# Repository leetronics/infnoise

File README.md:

### Infinite Noise TRNG (True Random Number Generator)

For instructions for compiling the and using Infinite Noise TRNG driver, go to the software
sub-directory, and read the [README](software/README.md) file there.  Both Linux and Windows
are supported.

The Infinite Noise TRNG is a USB key hardware true random number generator.  It uses what
I call a "Modular Entropy Multiplier" architecture (previously Infinite Noise Multiplier or
FireBug).  Besides being simple, low-cost, and fast, it is much easier to get right than
other TRNGs.  It naturally defends against influence from outside signals, such as radio
interference and power supply noise, making it simple to build securely, without requiring
an expert in analog design.  Modular entropy multipliers produce a provable and easily
measured level of entropy based on thermal noise, approximately equal to log2(K) per
output bit, where K is a gain between 1 and 2 set by two resistors around an op-amp.  A
"health monitor" can track this and verify that the output entropy is within the expected
range, which for the Infinite Noise TRNG described below is within 2% of log2(1.82).

Modular entropy multipliers are suitable for both board level implementation and ASIC
implementation.  Speed is limited by the speed of a gain stage and a comparator, and can
run in excess of 100 Mbit/second per second with high performance components.  Cheap
solutions with CMOS quad op-amps can run at 8Mbit/second.

Adjacent bits from a modular entropy multiplier are correlated, so whitening is required
before use in cryptography.  This should be done by continually reseeding a
cryptographically secure hash function such as SHA-512, Blake2b, Keccak-1600 (SHA3), or a
stream cipher such as ChaCha.  This implementation uses Keccak-1600 with cryptographically
secure reseeding of more than 400 bits of entropy at a time, overcoming a trickle in/out
problem present in the GNU/Linux /dev/random system.  Users who need many megabytes per second
of data for use in cryptography can set the outputMultiplier as high as they like, which
causes Keccak to generate outputMultiplier\*256 bits per reseeding by the Infinite Noise
TRNG.

The modular entropy multiplier architecture was invented by Peter Allan in 1999, which he
called [Firebug](http://apa.hopto.org/firebug).  I reinvented it in 2013.  As usual, most
of my good ideas are rediscoveries of existing ideas :-)  Peter has his own
version called [the Redoubler](https://github.com/alwynallan/redoubler), which
is awesome.  It really is the _right_ way to generate random bits, whether on a
board with standard parts, or on an custom chip.

### Crowd Supply campaign

With the aid of crowdfunding, the Infinite Noise will soon be produced (again)! The campaign is driven by Manuel Domke, founder of a fresh electronics manufacturing company called 13-37.org electronics. 

[Check the Crowd Supply project page for latest updates](https://www.crowdsupply.com/13-37/infinite-noise-trng)

### The Eagle open-source boards work!

Here is the first completed Infinite Noise USB key.  I offered this model on
Tindie to help get the modular entropy multiplier concept out there initially.

Here are the first three boards from OSH Park.  They work _exactly_ as predicted.  They all
generate 300,000 bits per second, resulting in a measured 259,000 bits of entropy per second, which is within 0.5% of the predicted value of log2(1.82).

All three boards should produce log2(1.82) = 0.864 bits of entropy per bit by design.  The first one is estimated
to produce 0.867, while the second one produces 0.868, and the third is 0.867.

Here is the latest schematic:

![Schematic of Infinite Noise Multiplier](images/infnoise.png?raw=true "Infinite
Noise Multiplier")

Here is the latest board layout (thanks, EagleWorks!):

![Board layout of Infinite Noise Multiplier](images/infnoise_brd.png?raw=true "Infinite
Noise Multiplier")

The breadboard worked, too.  Estimated entropy per bit is 0.81 for the bread-board.  By design, it should
be 0.80, so it is very close to the prediction.  The breadboard proved out much of the theory of operation, as well os providing raw data for entropy testing.

![Breadboard of Infinite Noise Multiplier](images/infnoise_breadboard.jpg?raw=true "Infinite
Noise Multiplier")

Here is the voltage on one of the hold cap:

To build one of these for yourself, you can [order three boards from OSH Park for only
$3.25](https://oshpark.com/profiles/WaywardGeek), and then buy parts from [Digikey and
Mouser as described in the
BOM](https://github.com/waywardgeek/infnoise/blob/master/eagle/BOM.xlsx?raw=true).  I
designed this board to be cheap, not easy to assemble by hand.  I use 2 QFN parts and
three with 0.5mm lead pitch.  If you want to [build these yourself the way I
do](https://www.sparkfun.com/tutorials/59), consider uploading the [infnoise.brd
file](https://raw.githubusercontent.com/waywardgeek/infnoise/master/eagle/infnoise.brd) to
[OSH Stencils](https://www.oshstencils.com/) and ordering a solder paste stencil for $7.
I get the [solder paste from SparkFun](https://www.sparkfun.com/products/12878).  Kudos to
OSH Park, OSH Stencil, SmallBatchAssembly, and DigiSpark!  They're making this whole party
possible!

The total for all the parts, including boards from OSH Park, come to $5.69 each, in 1,000
unit quantities.  However, that cost is dominated by USB related parts, particularly the
FT240X chip, the USB connector, and the USB-stick enclosure.  Just the components for the
modular entropy multiplier come out to $0.97.

Cor van Wandelen was kind enough to create these scatter plots showing the non-randomness
in the raw output.

Here is a faster version that uses a more expensive op-amp from TI:

![Schematic of Infinite Noise Multiplier](infnoise_small/schematic.png?raw=true "Infinite
Noise Multiplier")

### The Problem: Noise Sensitivity, and Signal Injection

True random number generators are very difficult to get right.  Generally, they amplify a
tiny noise signal, perhaps only a microvolt in amplitude, by a factor of millions or
billions, until the signal is an unpredictable digital signal.  This signal is then
sampled to see if it's a 0 or 1.

The problem with this approach is the weak noise source can easily be influenced by other
nearby signals, which may be under the control of an attacker, or perhaps observable by an
attacker, enabling him to predict the output.  Systems built with massive amplification of tiny noise sources often require power supply filters and EMI shielding, and even then remain difficult to prove secure.  Generally, an expert analog designer is needed to get it right.

Intel's RDRAND instruction is a perfect example.  It uses rapid amplification of thermal
noise to determine the power-up state of a latch.  Unfortunately, this source of entropy
is highly power-supply and cross-talk sensitive.  Intel claims to have
carefully shielded their thermal noise source, but without a thorough pubic audit of both
the design and layout, including all potential sources of interference, it is not possible
to trust the RDRAND instruction as the source of entropy for cryptography.

With such strong sensitivity, these TRNG architectures are potential targets for signal
injection by an attacker, who can cause the TRNG to generate his desired output rather
than true random data.

### The Solution: Modular Multiplication

Unpredictable noise sources are tiny, and must be massively amplified to be used by an
TRNG.  Other TRNG architectures amplify these signals until they saturate, becoming
digital 1's and 0's.  They rely on careful design and shielding to keep outside signals
from influencing the noise source.

For example, if we amplify a tiny noise source by 1 billion in a system that saturates at
3.3V, then 1uV of noise will be amplified causing the output to be about 3.3V.  An
attacker need only introduce at least -1uV to cause the TRNG to saturate at 0V instead.
An attacker with even this tiny influence can entirely control the output.

If TRNGs used modular multiplication to amplify their noise source, this noise sensitivity
problem would go away.

If we multiply a 1uV peak by 1 billion modulo 3.3V, then the result will be about 0.3V,
which will result in a digital 0.  If an attacker subtracts 1uV, causing our noise source
to be at 0.0V, then after amplification, the output is 0V, which still results in a 0.  In
fact, without knowing the current amplitude of the noise source, there is no signal an
attacker can add to our noise source to control the output.  He may be able to flip the
output bit, but since it was already random, his signal injection fails to control the
result, which is still random.  In fact, an attacker's injected signal causes the output
to be _more_ random, since an attacker is a nice unpredictable source of entropy!
Infinite Noise Multipliers _add_ entropy from all noise sources, even those from an
attacker.

### Variations

There are currently 3 versions of Infinite Noise Multipliers documented here.  The
infnoise_small directory describes a low part-count design that works well with op-amps
which have rail-to-rail inputs and outputs.  It runs at 4MHz, outputting 0.86 bits worth of
entropy on each clock (loop gain = 1.82), for a total of over 3.4 Mbit of entropy produced
per second.  The infnoise_fast directory contains a 50% faster design that uses a few more
resistors and an additional op-amp.  This design is suitable for use with a wide range of
op-amps.  It runs at 6MHz, outputting 0.86 bits worth of entropy on each clock (loop gain =
1.82), for over 5Mbit of entropy per second.

Because Infinite Noise Mulitpliers are switched-capacitor circuits, it is important to use
components with low leakage, like the OPA4354 CMOS quad op-amp from TI.  Op-amps with
below 1nA of input bias current will enable running at lower frequencies with less power.

To reproduce these simulations, download the TINA spice simulator from Ti.com.

Here is a "small" modular entropy multiplier:

![Schematic of small Infinite Noise Multiplier](infnoise_small/schematic.png?raw=true "Small
Infinite Noise Multiplier")

Note that the upper left op-amp is used as a comparator, and must settle to either 0V or
Vsup before the lower left op-amp can multiply the input by 2X.

Here's a "fast" version that does two multiplications in parallel and uses the comparator
result to select the right one.

![Schematic of fast Infinite Noise Multiplier](infnoise_fast/schematic.png?raw=true "Small
Infinite Noise Multiplier")

There is also a [CMOS version described here](http://waywardgeek.net/RNG).

### Simulations

LTspice was used to simulate the small and fast variations.  Here are simulation waveforms
for the small version:

![Simulation of small Infinite Noise Multiplier](infnoise_small/shortsim.png?raw=true "Small
Infinite Noise Multiplier")
![Simulation of small Infinite Noise Multiplier](infnoise_small/longsim.png?raw=true "Small
Infinite Noise Multiplier")

And again for the fast version.

![Simulation of fast Infinite Noise Multiplier](infnoise_fast/shortsim.png?raw=true "Fast
Infinite Noise Multiplier")
![Simulation of fast Infinite Noise Multiplier](infnoise_fast/longsim.png?raw=true "Fast
Infinite Noise Multiplier")

### Theory of Operation

Consider how a successive-approximation A/D converter works.  Each clock cycle, we compare
the input voltage to the output of a D/A converter, and if it's higher, the next bit out
is 1, and if lower, it's a 0.  We use binary search to zero-in on the analog input value.
Here is a block diagram from Wikipedia:

![Successive approximation A/D block diagram](images/SA_ADC_block_diagram.png?raw=true "SAR
A/D Block Diagram")

There is another way to build a successive-approximation A/D that eliminates the D/A
converter.  Compare the input to Vref (1/2 supply), and if it is larger, subtract Vref
from the input.  Then multiply by 2X.  The bit out is the value of the comparator.

    Vin' = Vin >= Vref? Vin - Vref : Vin

This eliminates the D/A converter, and has no limit on how many bits we shift out.  In
reality, the only reason we do not use this architecture for real A/D converters is that
it's accuracy depends on the accuracy of the multiply by 2X operation.  A simple circuit
with 1% resistors would only achieve about a 7 bit resolution.

However, just because the bits are not accurate does not mean we can't keep shifting them
out.  What are we measuring after shifting 30 times?  It's just noise in the circuit, with
no correlation to the original Vin.  It's totally random unpredictable nonsense.  This is
the idea behind the Infinite Noise Multiplier.

If this A/D converter was perfect, both 0's and 1's should shift out with equal
probability, with no correlation between bits.  This has been verified C simulations and
dieharder.  However, due to accuracy limitations on real components, we cannot multiply by
exactly 2X every cycle.  When the loop amplification is < 2X, the entropy per output bit
is reduced, but can be easily computed.  If E is the entropy per bit, and K is the loop
amplification, then:

    E = log(K)/log(2)

or equivalently:

    E = log2(K)

This provides a simple way to calculate the entropy added to an entropy pool per bit.
The program infnoise.c directly measures the entropy of modular entropy multiplier output,
and compares this to the estimated value.  Both simulations and actual hardware show that
they correlate well.

The "fast" board level version uses two op-amps and comparator to impliment a modular
multiplication using a couple of tricks.  First, multiplication by 2 modulo Vsup is
accomplished by multiplying relative to either GND or Vsup.  When multiplying relative to
GND, a 0.2V signal becomes 0.4V.  When multiplying relative to a 3V Vsup, a 2.8V signal
becomes 2.6V, because 2.8V is 0.2V below 3V, and after 2X, it's 0.4V below 3V.  The math
comes out the same as if I'd multiplied relative to GND, and simply subtracted Vsup if the
result was > Vsup:

    Vsup - 2*(Vsup - Vin) = Vsup - 2*Vsup + 2*Vin = 2*Vin - Vsup
        = 2*Vin mod Vsup

So, we multiply by 2 either way, and only subtract out Vsup if needed.  This is identical
to multiplication modulo Vsup.  The comparator simply selects the output of one of the two
op-amps.  This is the basic analog modular multiplier.

A second trick used to create the "small" version was to notice that the output of the
comparator could be used to combine both multiplier op-amps into 1.  This abuse of the
comparator output needs to be carefully checked.  In particular, the output is generally
treated as a digital signal, but in this case, it is used as an analog singal.  Care
should be taken not to load the OUT signal significantly.

### Provable Entropy, Based on Thermal Noise

The RMS thermal noise generated by a resistor of value R is:

    Vnoise = sqrt(4*Kb*T*deltaF*R)

where Kb is Boltzmann's constant 1.3806504×10-23 J/K, T is temperature in Kelvin (about
293 for room temperature), and deltaF is the frequency range of noise being measured.

For the V1 version of the Infinite Noise boards above, the op-amp has an 8MHz unit gain
crossover, and a low load negative input with 10K Ohms in parallel with 8.2K Ohms, which
is 4.5K Ohms.  Vnoise up to unity crossover is about 24uV, and gets amplified by the
op-amp gain K of 1.82 to about 40uV, and held on a 220pF capacitor.  A 40uV change on the
hold capacitors results in a current of about 55,000 electrons, so the hold capacitors are
able to capture about 15 bits of resolution of this noise signal, which gets amplified by
K and combined with later noise samples in the hold capacitors every cycle.  The
capacitors s hold about 2^31 different charge levels in the range of 0.3V to 3V.  This is
effectively a 31-bit register which we multiply by 1.82 every cycle and add a 15 bit noise
signal.  This results in entropy shifted out just slightly less than log2(1.82), since
this entropy compression does not result in 100% pure entropy (just very close).

changes the output of the comparator several cycles later.  Each cycle, this 15-bit noise
signal is added in, far in excess of the log2(K) of entropy we shift out, enabling us to
concentrate entropy in the hold capacitors, which hold over 2^32 electrons when
discharging from the design range of 3V to 0.3V.  Note that we are not assuming successive
noise samples of this 8MHz noise, when measured at 480KHz, will be completely uncorrelated,
but only that concentrating a 15-bit representation of sequential samples will have a few
bits of "surprise", which is log2(1/probability of guessing the next sample).

### Analysis of Analog Modular Multiplication

Consider a traditional zener TRNG:

    Vzener -> Multiply by 1e9 relative to Vref -> Clamp between -Vsupply and Vsupply -> digital 0/1

For simplicity, assume our amplifier has positive and negative supplies, Vsupply, and
-Vsupply.  If Vzener\*1e9 >= 0, then the output is a digital 1, otherwize 0.

There are variations on this theme, but this is basically how Zener TRNGs work.  The math
computed by this circuit is:

    clamp(-Vsupply, Vsupply, 1e9*Vzener)

where the first two parameters are the lower and upper clamping voltages, and the third
parameter is the amplified signal.

The problem with this design is that an attacker, Malory, can override the tiny zener
noise source with radio-signals, or any of a number of attacks.  Basically, if he can find
a way to add his signal to Vzener, then the circuit does this:

    clamp(-Vsupply, Vsupply, 1e9*(Vzener + Vmallory))

If Vmallory is always just a bit larger than Vzener in magnitude, then Mallory can
completely determine the output, because Mallory can make Vzener + Vmallory greater or
less than zero at will, and after multiplying by 1e9 it the amplifier will saturate in the
direction of the sign of Vmallory.

What if we used modular multiplication instead?  Assume we represent Vzener now as a
positive voltage between 0 and Vsupply so we can use the normal mod operation.  In this
case the normal output would be:

    Vzener*1e9 mod Vsupply -> compare to Vsupply/2 -> 1 if > Vsupply/2, 0 otherwise

This is even _more_ unpredictable than the original version. Only the portion of Vzener
between +/- Vsupply/1e9 made any difference in the output before, but now we use the
entire amplitude of Vzener.  The amplitude of Vzener has additional entropy which now
further whitens the output bit.

When Mallory attacks this system, injecting Vmallory into the same node as Vzener, it
computes:

    (Vzener + Vmallory)*1e9 mod Vsupply = Vzener*1e9 + Vmallory*1e9 mod Vsupply

Let Vz = Vzenner\*1e9 mod Vsupply, and Vm = Vmallory\*1e9 mod Vsupply.  Then the output
is just:

    Vz + Vm mod Vsupply

Vz is unpredictably distributed between 0 and Vsupply, hopefully somewhat uniformly.
How can Mallory determine what to add to it to control the output?  He can not.
His interference can only _increase_ the entropy of the output, since Mallory's attack is
itself an entropy source, further randomizing the result.

### Rolling Up the Loop

A 30-long cascade of switched capacitor 2X modular multipliers is a lot of hardware!
Fortunately, it is possible to reuse the same multiplier for each stage, without even
slowing down the circuit.  In our long chain of 2X modular multipliers, we computed:

    A1(1) = 2*Vzener(0) mod Vsupply
    A2(2) = 2*A1(1) mod Vsupply
    A3(3) = 2*A2(2) mod Vsupply
    ...
    A30(30) = 2*V29(29) mod Vsupply

Here, Vzener(0) is Vzener when sampled at the first clock pulse.  Vzener(n) is the voltage
sampled on the nth clock pulse.  An(i) is the output of the nth 2X modular multiplier at
clock cycle i.  Instead of using 30 stages, what would happen if we simply fed the output
of the 2X modular multiplier stage back on itself?  We'd just have A instead of A1 ..
A30:

    A(1) = 2*Vzener(0) mod Vsupply
    A(2) = 2*(Vzener(1) + A(1) mod Vsupply 
          = 2*Vzener(1) + 4*Vzener(0) mod Vsupply
    A(3) = 2*(Vzener(2) + A(2)) mod Vsupply
          = 2*Vzener(2) + 4*Vzener(1) + 8*Vzener(0) mod Vsupply
    ...
    A(30) = 2*Vzener(29) + 4*Vzener(28) + 8*Vzener(27) + ... + 2^30*Vzener(0) mod
    Vsupply

If 2^30\*Vzener(0) mod Vsupply is an unpredictable value, then the other terms can in no
way reduce this unpredicability.  What if Mallory attacks?  In that case, at step 30, we
have:

    A(30) = 2*(Vzener(29) + Vmallory(29)) + ... + 2^30*(Vzener(0) + Vmallory(0) mod
    Vsupply
            = [2*Vzener(29) + 4*Vzener(28) + ... + 2^30*Vzener(0)] +
              [2*Vmallory(29) + 4Vmallory(28) + ... + 2^30*Vmallory(0)] mod Vsupply

The output is just the signal we had before without Mallory's influence, plus a value
injected by Mallory, mod Vsupply.  Once again if Mallory does not know what the value of
A(30) would have been, he cannot control the result.  He can only make it more random.

The value of A acts as an entropy pool, collecting entropy from all signals that impact
it's value.

### We Don't Need Zener Noise

In reality, there are many sources of unpredictable noise in every circuit.  There's large
predictable and controllable noise, like power supply noise, and tiny 1/f noise in the
multi-gigahertz range.  Shot noise, thermal noise, EMI, cross-talk... you name it, no
matter where we look, there's noise.  Infinite noise multipliers amplify them all in
parallel, and adds them together effectively in an tiny entropy pool.  Zener noise would
be just one more source of noise in a symphony of existing noise sources, and will not
enhance the resulting entropy enough to bother.

A modular entropy multiplier will amplify _every_ source of niose and amplify it until it is
larger than Vsupply.  It adds them together and amplifies them in parallel.  Every device
in the signal path loop contributes. 

With N sources of noise, the output looks like:

    V1(1) = Vnoise1(1) + Vnoise2(1) + Vnoise3(1) ... VoinseN(1)
    ...
    V1(30) = [2*Vnoise1(29) + 4*Vnoise1(28) + ... + 2^30*Vnoise1(0)] +
             [2*Vnoise2(29) + 4*Vnoise2(28) + ... + 2^30*Vnoise2(0)] +
             ...
             [2*VnoiseN(29) + 4VnoiseN(28) + ... + 2^30*VnoiseN(0)] mod Vsupply

Each individual noise sources contributes its own power-of-two sequence to the total.
A micro-volt noise source contributes nearly as strongly as a Vsupply/10 amplitude noise
source.

The mashing together of noise source data with unbounded modular multiplications leads to
awesome entropy levels.  Just how awesome?  Consider just thermal noise from one resistive
summing node (the minus terminal on op-amp in the 2X gain stage).

How correlated are successive samples?  How badly does this impact our output?  It turns
out that high correlation is OK.  What we want is high resolution contribution of noise
samples, even more than low correlation.

Suppose sample Vnoise(0) is 1.034 uV, and Vnoise(1) is 1.019 uV.  That is
some bad correlation, but 14 clock cycles later, the difference in amplitudes between
these samples will have the output toggling unpredictably.  What matters is not
correlation between noise samples, but the accuracy to which we can remember the
difference between them in our circuit.  This should be limited only by electron counts on
our hold capacitor.  It has an integer number of electrons at any time.  About 2.5 billion
electrons flow out of 100pF holding caps when charging from 0.5V to 4.5V.  That's about 31
bits of resolution.  Every time we capture noise on these caps, it adds or subtracts an
integer number of electrons.  Each electron contributes about 1.6nV on our hold cap.  So
long as we can capture noise that has significantly more than 1.6nV of unpredictability,
we should be able to keep the output generating close to 1 bit of entropy per clock.  In
this example, both noise samples had over 10X the minimum resolution in unpredictable
noise, and easily contributed a bit of entropy each to our 31-ish bit entropy pool.

### Whitening the Right Way

Data coming from true random number generators is never 100% random.  I am aware of no
exceptions.  Whitening is required in all cases before the data is suitable for use in
cryptography.

Most TRNGs build whitening into the hardware.  This is a _mistake_, at least if the
whitening cannot be turned off.  Respectable TRNGs, such as [OneRNG](http://onerng.info/)
and [Entropy Key](http://www.entropykey.co.uk/) provide hardware whitening, but also
provide access to the raw data streams for health analysis.

I prefer to follow the KISS rule when it comes to security.  The more complex the TRNG
key, the more likely it is insecure.  Therefore, the initial Infinite Noise Multiplier
does not even have a microcontroller onboard, and only returns raw data, direct from the
noise source.  Whitening is done in the Infinite Noise driver.

The Infinite Noise driver uses the reference version of the SHA3 "sponge", called Keccak,
with a 1600 bit state.  To make the state of the sponge unpredictable, it is initialized
with 20,000 bits of of Infinite Noise data before any data is output.  After that, reading
bytes from the SHA3 sponge blocks until twice as many bytes of entropy have been fed into
the sponge from the Infinite Noise TRNG.

### Non-Power-of-Two Multiplication

The circuit shown in infnoise_fast multiplies by 1.82 every clock rather than 2.0.  As
stated above, this reduces the entropy per output bit to log(1.82)/log(2) = 0.86 bits of
entropy per output bit.

Suppose in cycle 0, the noise Vnoise(0) is +/- Vsupply/2^30V every cycle.  At most 31 clock
cycles can go by before the output toggles due to Vnoise(0), because on cycle 31, it's
contribution will be 2\*Vsupply, and the remaining noise contributions can do no more than
subtract Vsupply.  This will have to be subtracted out.  The cycle x1 where we know
Vnoise(0) will have toggled the output is:

    Vnoise(0)*2^x1 >= 2*Vsupply
    2^x1 >= 2*Vsupply/Vnoise(0)
    x1 >= log(2*Vsupply/Vnoise(0))/log(2)

When multiplying by K, where 1 < K < 2, it takes more clock cycles for Vnoise(0) to reach
Vsupply, insuring that it will have changed the output.  The cycle x2 when this happens
is:

    Vnoise(0)*K^x2 >= 2*Vsupply
    K^x2 >= 2*Vsupply/Vnoise(0)
    x2 >= log(2*Vsupply/Vnoise(0))/log(K)

The ratio of the clocks it takes with amplification 2 vs K is:

    x1/x2 = [log(Vsupply/Vnoise(0))/log(2)] / [log(Vsupply/Vnoise(0))/log(K)]
          = log(K)/log(2)

It takes log(2)/log(K) more cycles to insure the output is different.
the entropy shifted out with exactly 2X amplification will be 1 bit per clock.

### Health Monitoring

Infinite Noise Multipliers output entropy at a predictable rate, which is measured
continually.  If the entropy per bit deviates from the theoretical value of log(K)/log(2)
by more than 2% during the previous 80,000 bits, then the driver stops generating output.
Some deviation is expected, since K is dependent on two resistor values, which can be off
by 1% each.  Also, a significant amplitude noise in the system, as well as "misfires", can
cause more entropy to be output than predicted.  The estimated entropy per bit are
continually estimated and compared to expected values.

Entropy per bit is measured as the log2 of one over the probability of seeing a specific
output sequence from the modular entropy multiplier.  The probability of any given output
bit is estimated by keeping a history of results, given the previous 7 bits.  Simulations
with K=1.82 show that using 16 bits rather than 7 gives only a 0.16% improvement in
prediction accuracy, so only 7 are used.

### Entropy Testing

A common program used to estimate entropy in a data stream is "ent".  A sample data file
was created this way (using one of the original V1 boards):

    $ sudo ./infnoise-v1 --raw --debug > foo
    ...
    Generated 14680064 bits.  OK to use data.  Estimated entropy per bit: 0.866710, estimated
    K: 1.823500
    num1s:49.888504%, even misfires:0.159748%, odd misfires:0.127300%
    Generated 15728640 bits.  OK to use data.  Estimated entropy per bit: 0.866856, estimated
    K: 1.823684
    num1s:49.901504%, even misfires:0.145973%, odd misfires:0.160365%
    Generated 16777216 bits.  OK to use data.  Estimated entropy per bit: 0.867010, estimated
    K: 1.823879
    num1s:49.963040%, even misfires:0.146815%, odd misfires:0.145067%

Here's ent's results on the raw data stream this run produced:

    $ ent foo
    Entropy = 7.318058 bits per byte.
    
    Optimum compression would reduce the size
    of this 2072576 byte file by 8 percent.
    
    Chi square distribution for 2072576 samples is 1510131.51, and randomly
    would exceed this value 0.01 percent of the times.
    
    Arithmetic mean value of data bytes is 127.5088 (127.5 = random).
    Monte Carlo value for Pi is 3.427100794 (error 9.09 percent).
    Serial correlation coefficient is -0.005035 (totally uncorrelated = 0.0).

The health monitor does a much better job at estimating the entropy than ent.  The actual
non-randomness is 60% higher than ent predicted.  Ent said 0.915 bits of entropy per bit,
while the health monitor measured 0.867.  The health monitor's entropy estimator is just a
tiny fraction of a percent higher than the model predicts, while ent is off by 4.8% .  The
design target for entropy per bit was log2(1.82) = log(1.82)/log(2) = 0.864.  This is set
by two resistors.  Based on entropy measured by the health monitor, it could compress this
file by 13.3%.

The entropy estimator is based on the model that:

- The device is not rapidly changing the sort of numbers it puts out, so history can be
  used as a guide.
- There is no special state stored in the modular entropy multiplier that could cause data
  to be different each clock cycle, other than on even/odd cycles.
- Bits further away are less correlated.

The first assumption is strong assuming an attacker is not involved.  An attacker
injecting a strong signal could mount a DoS attack, since the health monitor would detect
entropy being too high, and would disable output.  This is a conscious choice: the health
monitor could instead simply warn that entropy seems too high.  Turning off the output
when an attacker may be present seems the safer choice.

The second assumption relies on the fact that only two nodes store state in this
implementation of a modular entropy multiplier, and that the outputs are sampled from
even/odd comparator outputs on even/odd cycles.  Other TRNGs may not satisfy this
assumption if they have additional internal state.  However, a typical zener TRNG should
satisfy this assumption.

The third assumption really does require a modular entropy multiplier.  A zener TRNG would
most likely have strong 60 Hz correlations from 60 Hz noise, for example.  This is also
true of A/D converter based TRNGs.  With a modular entropy multipliers, these signal sources
are added to a signal already saturated with thermal noise, making it in no less random.
Every cycle, a new thermal noise sample is added to the state, causing less correlation
with previous states.

### Future Version

I'm really just having fun with this project.  I personally prefer this version

I plan on only making this version going forward, even though I doubt it will sell very
well.  That's OK, because I don't make any money on them :-)

### Credits

Peter Allan has been very helpful in moving this project forward.  The github user known
as EagleWorks did an _amazing_ job redoing the board layout.  Somehow, my ameraturish work
just wasn't good enough for him :-)  Thanks, EagleWorks!  Cor van Wandelen created the
color and scatter plots.

### Free As in Freedom

The modular entropy multiplier architecture was invented in 1999 by Peter Allan, but was not
patented at that time.  Peter is working with me to make modular entropy multiplier/Firebug
open-source hardware, unencumbered by patents or copyright.

I reinvented with the modular entropy multiplier architecture in 2013, and the board level
versions in 2014.  I hereby renounce any claim to copyright and patent rights related to
any changes or improvements I may have made to this architecture.  Furthermore, I am aware
of no infringing patents and believe there are none.  It should be entirely safe for use
in any application.  Feel free to copy anything here, and even sell your own modular
noise multiplier based USB keys based on this work.

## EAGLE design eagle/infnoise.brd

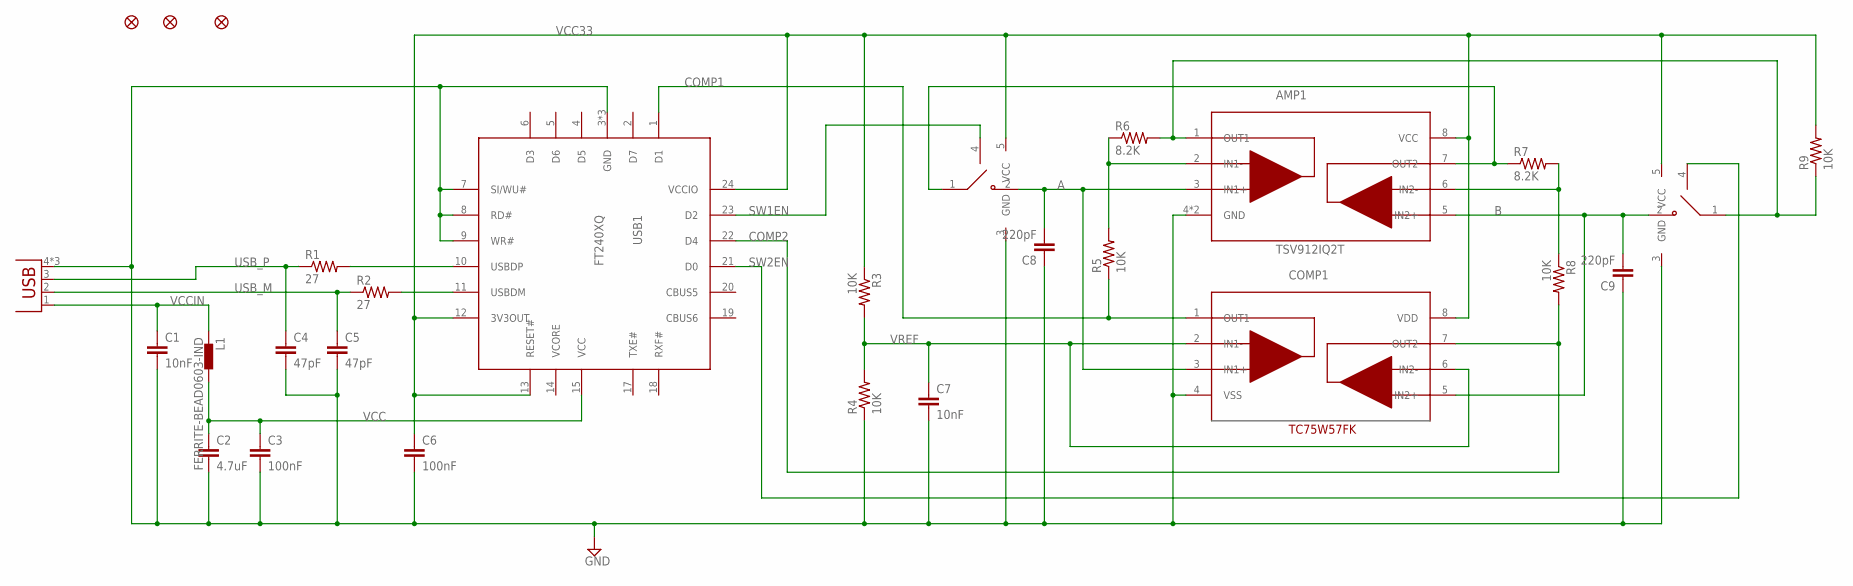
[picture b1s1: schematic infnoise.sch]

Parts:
AMP1: TSV912IQ2T; DFN8-2X3
C1, C7: 10nF; 0603-CAP
C2: 4.7uF; 0603-CAP
C3, C6: 100nF; 0603-CAP
C4, C5: 47pF; 0603-CAP
C8, C9: 220pF; 0603-CAP
COMP1: TC75W57FK; SSOP8-P-0.50A
FID1, FID2, FID3: FIDUCIALUFIDUCIAL; MICRO-FIDUCIAL
L1: FERRITE-BEAD0603-IND; 0603-IND
R1, R2: 27; 0603-RES
R3, R4, R5, R8, R9: 10K; 0603-RES
R6, R7: 8.2K; 0603-RES
SW1, SW2: MC74VHC1G66DFT1G; SC70-5L
USB1: FT240XQ; QFN24-4X4
X1: USBSMT-MALE; USB-A-SMT-MALE

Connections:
A: AMP1.3 (IN1+), C8.2, COMP1.3 (IN1+), SW1.2 (NO)
AMP1OUT: AMP1.1 (OUT1), R6.2, R9.1, SW2.1 (COM)
AMP2OUT: AMP1.7 (OUT2), R7.1, SW1.1 (COM)
B: AMP1.5 (IN2+), C9.2, COMP1.5 (IN2+), SW2.2 (NO)
COMP1: COMP1.1 (OUT1), R5.1, USB1.1 (D1)
COMP2: COMP1.7 (OUT2), R8.2, USB1.22 (D4)
FB1: AMP1.2 (IN1-), R5.2, R6.1
FB2: AMP1.6 (IN2-), R7.2, R8.1
GND: AMP1.4 (GND), AMP1.EXP (GND), C1.2, C2.2, C3.2, C4.2, C5.2, C6.2, C7.2, C8.1, C9.1, COMP1.4 (VSS), R4.1, SW1.3 (GND), SW2.3 (GND), USB1.3 (GND), USB1.7 (SI/WU#), USB1.8 (RD#), USB1.9 (WR#), USB1.16 (GND), USB1.EXP (GND), X1.4 (GND), X1.P$1 (GND), X1.P$3 (GND)
unnamed: R1.2, USB1.10 (USBDP)
SW1EN: SW1.4 (IN), USB1.23 (D2)
SW2EN: SW2.4 (IN), USB1.21 (D0)
USBDM: R2.2, USB1.11 (USBDM)
USB_M: C5.1, R2.1, X1.2 (D-)
USB_P: C4.1, R1.1, X1.3 (D+)
VCC: C2.1, C3.1, L1.2, USB1.15 (VCC)
VCC33: AMP1.8 (VCC), C6.1, COMP1.8 (VDD), R3.1, R9.2, SW1.5 (VCC), SW2.5 (VCC), USB1.12 (3V3OUT), USB1.13 (RESET#), USB1.24 (VCCIO)
VCCIN: C1.1, L1.1, X1.1 (VCC)
VREF: C7.1, COMP1.2 (IN1-), COMP1.6 (IN2-), R3.2, R4.2

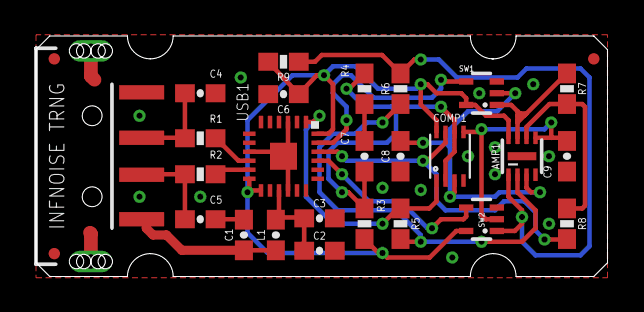
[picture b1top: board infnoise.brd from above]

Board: 2 copper layers, 31.8 x 13.4 mm, 28 parts (0 on the bottom side), 19 nets.

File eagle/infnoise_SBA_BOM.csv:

##########################################################################
       Name: Placement Bill of Materials Generator

    Version: 2
         By: Small Batch Assembly
        URL: www.smallbatchassembly.com
 SourceFile: infnoise.brd
   DateTime: 11/16/14 1:45 PM
      Units: inches
##########################################################################
REF,PACKAGE,VALUE,X,Y,ROTATION,
AMP1   , DFN6-2X3            , TSV912IQ2T     , 1.0630, 0.2630, 0.0
C1   , 0603-CAP            , 10nF     , 0.4547, 0.0908, 90.0
C2   , 0603-CAP            , 4.7uF     , 0.6201, 0.0563, 0.0
C3   , 0603-CAP            , 100nF     , 0.6201, 0.1272, 0.0
C4   , 0603-CAP            , 47pF     , 0.3593, 0.4008, 0.0
C5   , 0603-CAP            , 47pF     , 0.3593, 0.1252, 0.0
C6   , 0603-CAP            , 100nF     , 0.5413, 0.3988, 180.0
C7   , 0603-CAP            , 10nF     , 0.7185, 0.2630, 90.0
C8   , 0603-CAP            , 220pF     , 0.7972, 0.2630, 90.0
C9   , 0603-CAP            , 220pF     , 1.1614, 0.2630, 90.0
COMP1   , SSOP8-P-0.50A            , TC75W57FK     , 0.9055, 0.2630, 0.0
FID1   , MICRO-FIDUCIAL            , FIDUCIALUFIDUCIAL     , 0.0400, 0.0500, 0.0
FID2   , MICRO-FIDUCIAL            , FIDUCIALUFIDUCIAL     , 0.0400, 0.4760, 0.0
FID3   , MICRO-FIDUCIAL            , FIDUCIALUFIDUCIAL     , 1.2200, 0.4760, 0.0
L1   , 0603-IND            , FERRITE-BEAD0603-IND     , 0.5246, 0.0908, 90.0
R1   , 0603-RES            , 27     , 0.3593, 0.3024, 0.0
R2   , 0603-RES            , 27     , 0.3593, 0.2236, 0.0
R3   , 0603-RES            , 10K     , 0.7185, 0.1154, 90.0
R4   , 0603-RES            , 10K     , 0.7185, 0.4106, 90.0
R5   , 0603-RES            , 10K     , 0.7972, 0.1154, 270.0
R6   , 0603-RES            , 8.2K     , 0.7972, 0.4106, 90.0
R7   , 0603-RES            , 8.2K     , 1.1614, 0.4106, 270.0
R8   , 0603-RES            , 10K     , 1.1614, 0.1154, 270.0
R9   , 0603-RES            , 10K     , 0.5413, 0.4697, 180.0
SW1   , SC70-5L            , MC74VHC1G66DFT1G     , 0.9744, 0.4008, 90.0
SW2   , SC70-5L            , MC74VHC1G66DFT1G     , 0.9744, 0.1252, 90.0
USB1   , QFN24-4X4            , FT240XQ     , 0.5413, 0.2630, 270.0
X1   , USB-A-SMT-MALE            , USBSMT-MALE     , 0.0000, 0.2630, 90.0

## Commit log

2025-07-17 macos: fix unused param compiler warning/error
2025-08-26 make c file non-executable
2026-04-12 Add GitHub Actions workflow for automated package builds
2026-04-12 Add DKMS package build scripts
2026-04-12 Fix: invoke build scripts with bash to avoid dash incompatibility
2026-05-04 Fix UAF in kernel module by using kref, small fixes
2026-05-04 kmod: also log serial number
2026-05-04 kmod: simplify keccack usage
2026-05-04 kmod: allow recovery from temporary health failures
2026-05-04 kmod: fix deadlock in error path

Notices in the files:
parts and their libraries:
SparkFun-Aesthetics: Licensing: Creative Commons ShareAlike 4.0 International - https://creativecommons.org/licenses/by-sa/4.0
